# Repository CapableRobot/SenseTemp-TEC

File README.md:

# SenseTemp TEC

Designed by [Capable Robot Components](http://capablerobot.com).  
Follow us on [Twitter](http://twitter.com/capablerobot) for product announcements and updates.

---

**SenseTemp TEC is available for purchase at [CrowdSupply](https://www.crowdsupply.com/capable-robot-components/sensetemp) & [Mouser](https://www.mouser.com/ProductDetail/Crowd-Supply/cs-sensetemp-03?qs=sGAEpiMZZMsSgQ5oX0A7uhzs7btMGoRQYlEWJtksaKTgK6BSOcNH6Q%3D%3D).**  

## SenseTemp TEC Features 

## Specifications

## Feather Hosts

SenseTemp TEC is designed to mate with Adafruit Feather-compatible host modules, like:

* [Adafruit Feather M4 Express](https://www.adafruit.com/product/3857)
* [Adafruit Feather M0 Express](https://www.adafruit.com/product/3403)
* [Adafruit ESP32 Feather Host](https://www.adafruit.com/product/3405)

Note that the ES8266 Feather is **NOT** supported due to the limited IO on the ESP8266.  It does not have enough pins to support the four SPI devices of the SenseTemp.

## Software

## Hardware Revisions

* [CR2ERP](revisions/CR2ERP) : Released 2018-12-18.
	* Added high-side switch for fan control
	* Removed `!EN` pin as this product will not run off of battery power and there is no need to disable RTD converter chips.
	* Added 12v to 3v regulator (and disabled 5v to 3v regulator on host board).
	* Minor footprint changes.
	* Changed `PWM` pin for TEC control.
* [CRHVEF](revisions/CRHVEF) : Initial version released 2018-12-04.

## License Information

| **Type** | **License** |
| --- | --- |
| Hardware | Copyright Capable Robot Components 2018 <br><br>This documentation describes Open Hardware and is licensed under the [CERN OHL v1.2 or later](https://www.ohwr.org/licenses/cern-ohl/license_versions/v1.2). <br/><br/> You may redistribute and modify this documentation under the terms of the CERN OHL v.1.2.  This documentation is distributed WITHOUT ANY EXPRESS OR IMPLIED WARRANTY, INCLUDING OF MERCHANTABILITY, SATISFACTORY QUALITY AND FITNESS FOR A PARTICULAR PURPOSE. Please see the CERN OHL v.1.2 for applicable conditions |
| Software | [MIT License](tree/master/LICENSE.txt) |
| Documentation | [Creative Commons Attribution-ShareAlike](https://creativecommons.org/licenses/by-sa/4.0/) License |

More detailed information about the CERN License is available in the [license](license) folder and on the [CERN website](https://www.ohwr.org/projects/cernohl/wiki).

| **OSHW Certification** |

Coming Soon

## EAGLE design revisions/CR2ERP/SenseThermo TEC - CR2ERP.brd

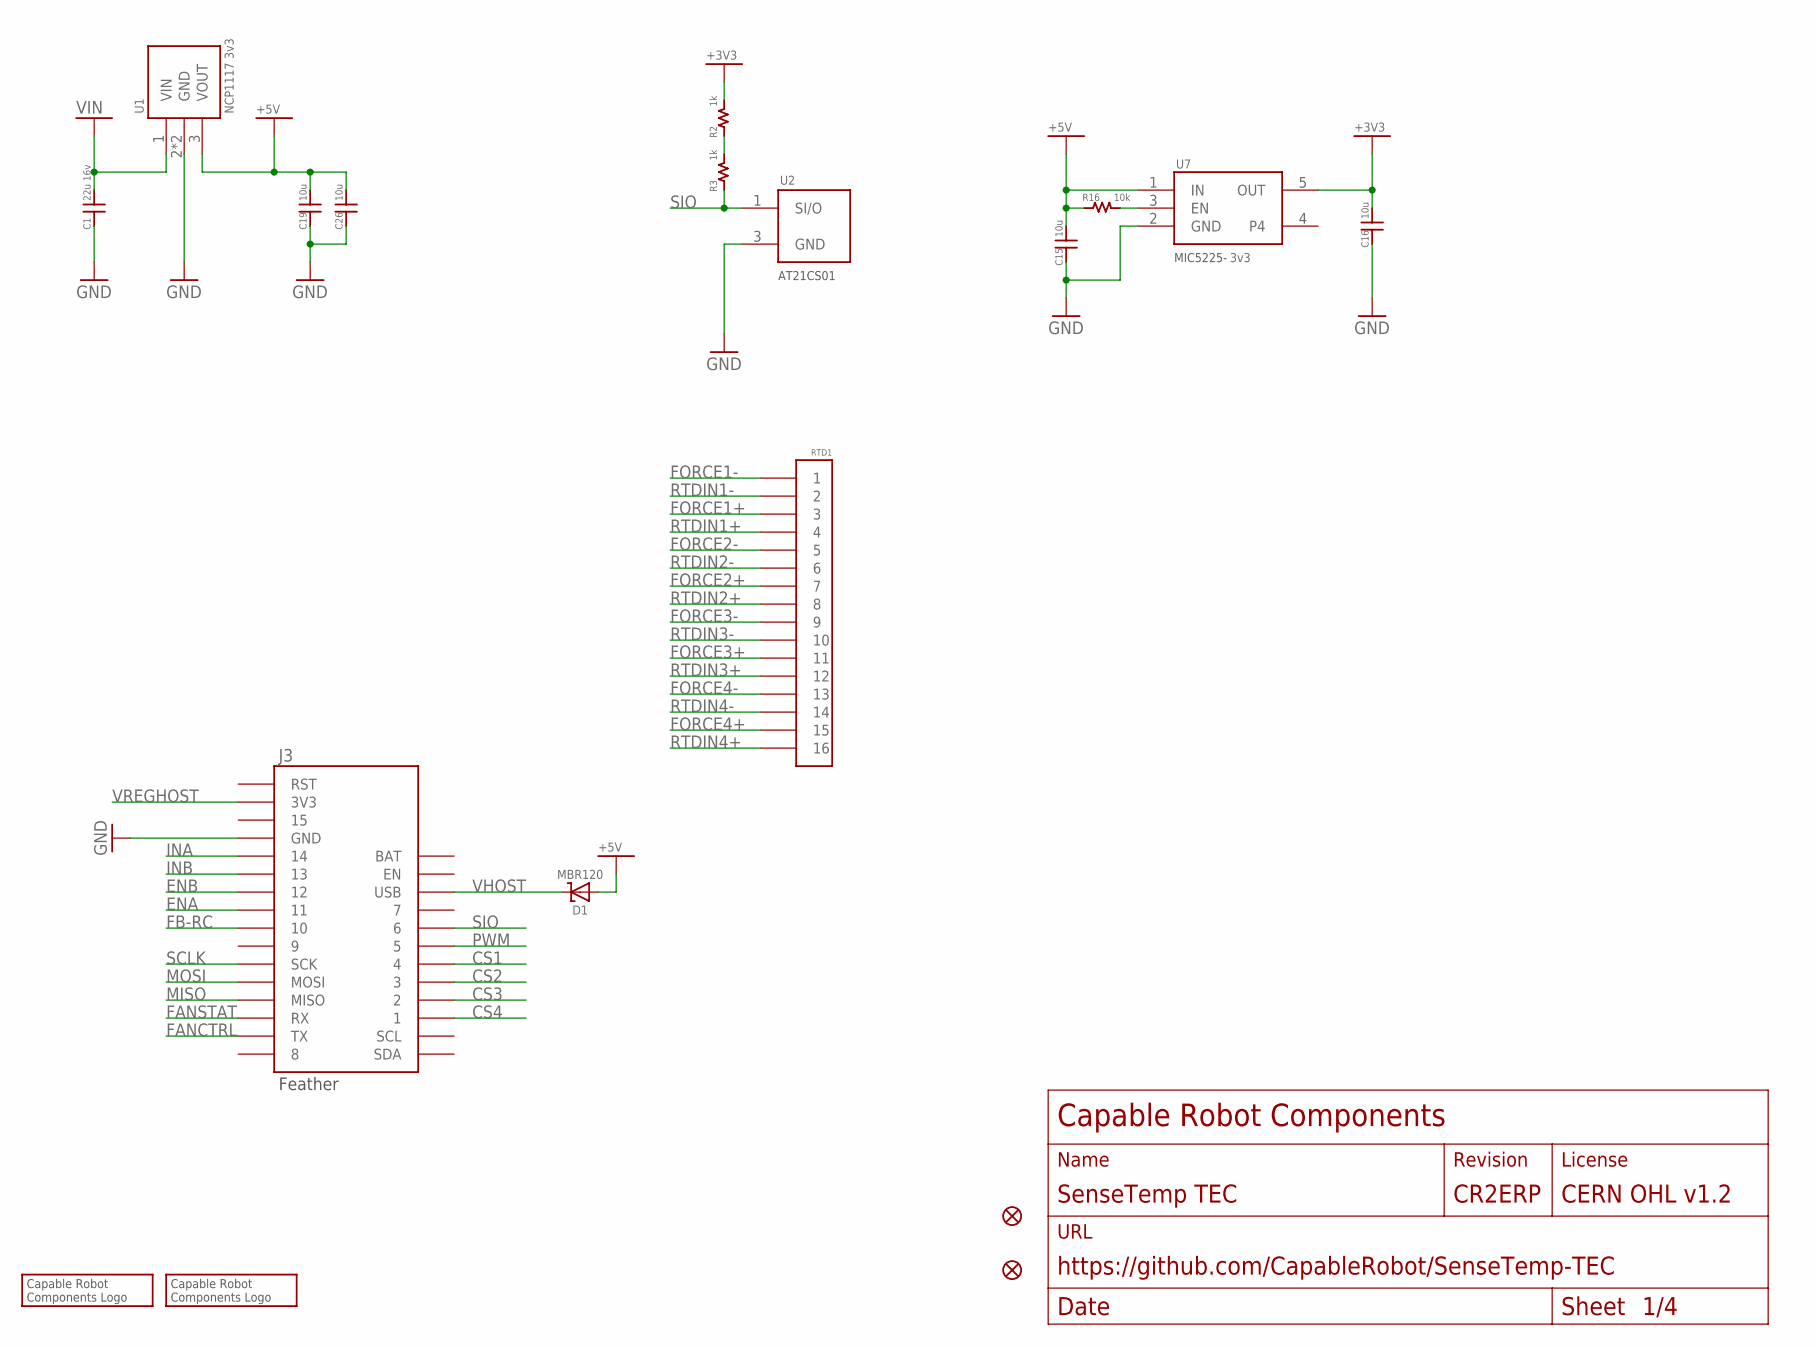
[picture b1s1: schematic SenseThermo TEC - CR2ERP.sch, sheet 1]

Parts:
C1: 22u 16v; 1206
C15, C16, C19, C26: 10u; 0805
D1: MBR120; SOD-123; MPN MBR120VLSFT3G
FID1, FID2: FIDUCIAL""; FIDUCIAL_1MM
J3: FEATHERPTH; FEATHER-PTH
LOGO1: CRC-LOGO7SILK; CRC-LOGO-7-SILK
LOGO2: CRC-LOGO5; CRC-LOGO-5
R2, R3: 1k; 0603
R16: 10k; 0603
RTD1: CONN-16ZT; CONN-2X8-050-SMT-ZT; MPN 3221-16-0300-00
U1: NCP1117 3v3; SOT230P700X180-4; MPN NCP1117ST50T3G
U2: AT21CS01; SOT23
U7: 3v3; SOT25

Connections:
+3V3: C16.P$2, R2.2, U7.5 (OUT); also elsewhere on the board
+5V: C15.P$2, C19.P$2, C26.P$2, D1.A, R16.1, U1.3 (VOUT), U7.1 (IN)
CS1: J3.4; also elsewhere on the board
CS2: J3.3; also elsewhere on the board
CS3: J3.2; also elsewhere on the board
CS4: J3.1; also elsewhere on the board
ENA: J3.11; also elsewhere on the board
ENB: J3.12; also elsewhere on the board
FANCTRL: J3.TX; also elsewhere on the board
FANSTAT: J3.RX; also elsewhere on the board
FB-RC: J3.10; also elsewhere on the board
FORCE1+: RTD1.3; also elsewhere on the board
FORCE1-: RTD1.1; also elsewhere on the board
FORCE2+: RTD1.7; also elsewhere on the board
FORCE2-: RTD1.5; also elsewhere on the board
FORCE3+: RTD1.11; also elsewhere on the board
FORCE3-: RTD1.9; also elsewhere on the board
FORCE4+: RTD1.15; also elsewhere on the board
FORCE4-: RTD1.13; also elsewhere on the board
GND: C1.P$1, C15.P$1, C16.P$1, C19.P$1, C26.P$1, J3.GND, U1.2 (GND), U1.4 (GND), U2.3 (GND), U7.2 (GND); also elsewhere on the board
INA: J3.14; also elsewhere on the board
INB: J3.13; also elsewhere on the board
MISO: J3.MISO; also elsewhere on the board
MOSI: J3.MOSI; also elsewhere on the board
unnamed: R2.1, R3.2
unnamed: R16.2, U7.3 (EN)
PWM: J3.5; also elsewhere on the board
RTDIN1+: RTD1.4; also elsewhere on the board
RTDIN1-: RTD1.2; also elsewhere on the board
RTDIN2+: RTD1.8; also elsewhere on the board
RTDIN2-: RTD1.6; also elsewhere on the board
RTDIN3+: RTD1.12; also elsewhere on the board
RTDIN3-: RTD1.10; also elsewhere on the board
RTDIN4+: RTD1.16; also elsewhere on the board
RTDIN4-: RTD1.14; also elsewhere on the board
SCLK: J3.SCK; also elsewhere on the board
SIO: J3.6, R3.1, U2.1 (SI/O)
VHOST: D1.C, J3.USB
VIN: C1.P$2, U1.1 (VIN); also elsewhere on the board
VREGHOST: J3.3V3; also elsewhere on the board

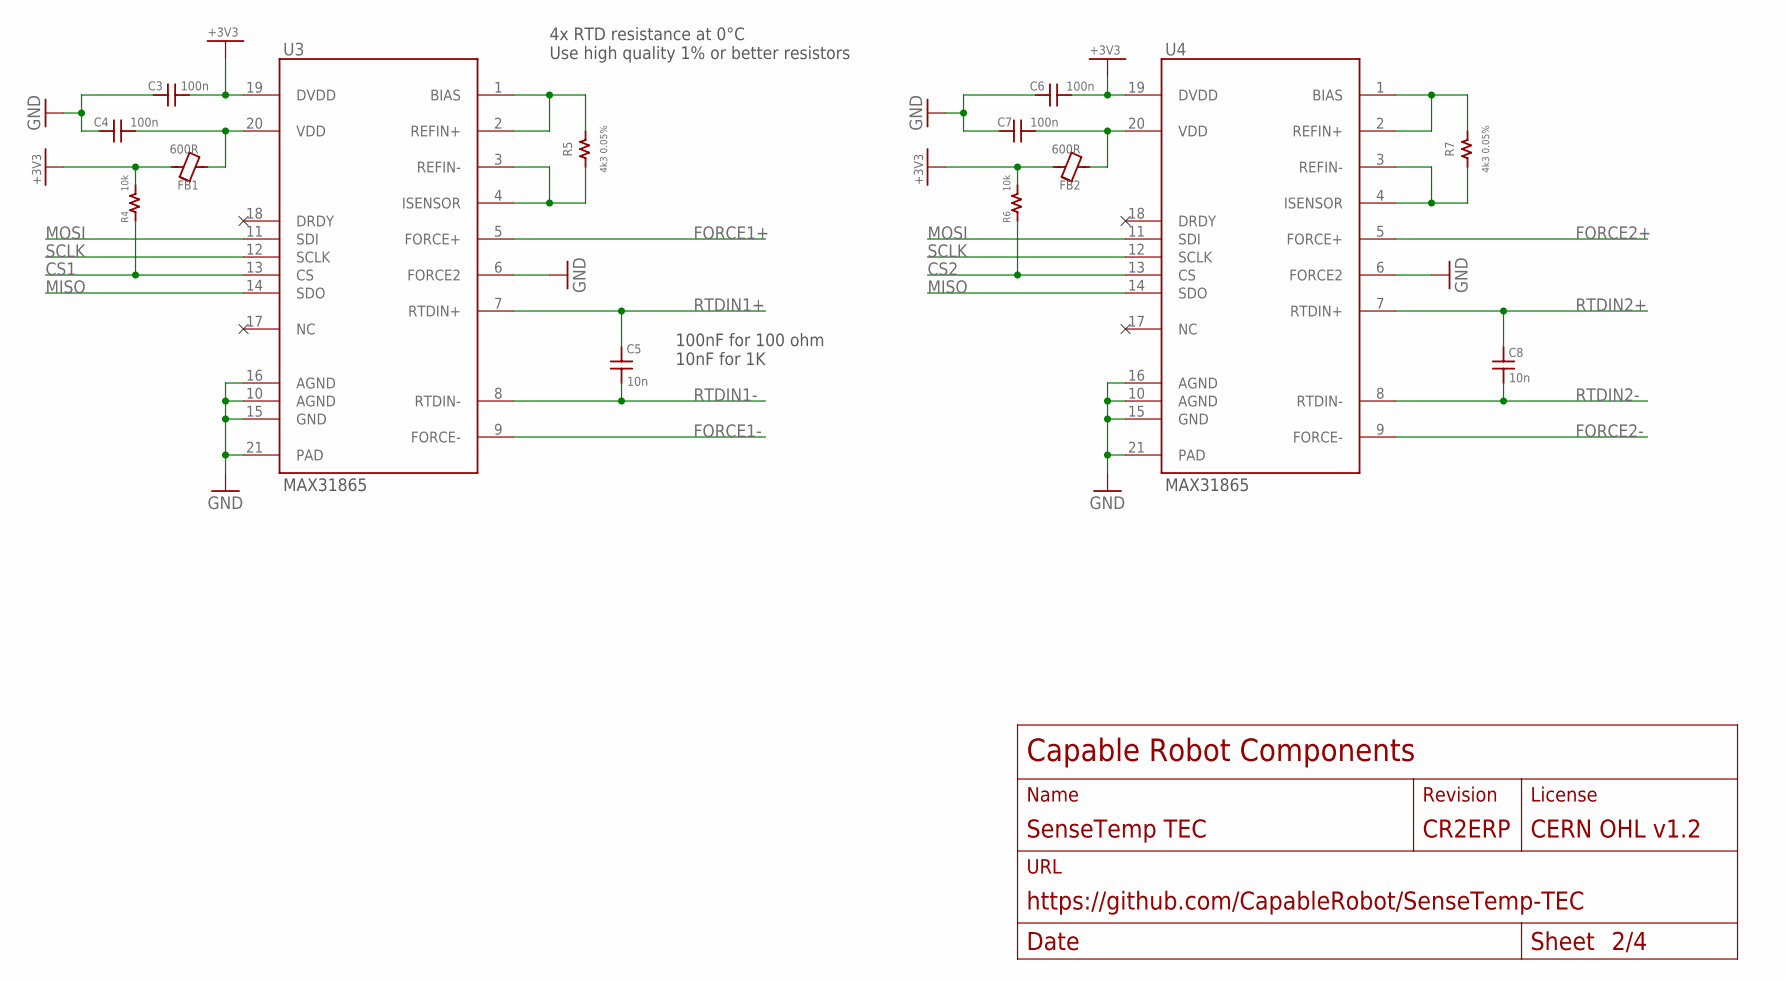
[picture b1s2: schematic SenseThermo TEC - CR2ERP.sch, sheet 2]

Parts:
C3, C4, C6, C7: 100n; 0603
C5, C8: 10n; 0603
FB1, FB2: 600R; 0603
R4, R6: 10k; 0603
R5, R7: 4k3 0.05%; 0603
U3, U4: MAX31865; QFN65P500X500X100-21T325

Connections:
+3V3: C3.1, C6.1, FB1.2, FB2.2, R4.2, R6.2, U3.19 (DVDD), U4.19 (DVDD); also elsewhere on the board
CS1: R4.1, U3.13 (CS); also elsewhere on the board
CS2: R6.1, U4.13 (CS); also elsewhere on the board
FORCE1+: U3.5 (FORCE+); also elsewhere on the board
FORCE1-: U3.9 (FORCE-); also elsewhere on the board
FORCE2+: U4.5 (FORCE+); also elsewhere on the board
FORCE2-: U4.9 (FORCE-); also elsewhere on the board
GND: C3.2, C4.2, C6.2, C7.2, U3.6 (FORCE2), U3.10 (AGND), U3.15 (GND), U3.16 (AGND), U3.21 (PAD), U4.6 (FORCE2), U4.10 (AGND), U4.15 (GND), U4.16 (AGND), U4.21 (PAD); also elsewhere on the board
MISO: U3.14 (SDO), U4.14 (SDO); also elsewhere on the board
MOSI: U3.11 (SDI), U4.11 (SDI); also elsewhere on the board
unnamed: R5.2, U3.1 (BIAS), U3.2 (REFIN+)
unnamed: R5.1, U3.3 (REFIN-), U3.4 (ISENSOR)
unnamed: C4.1, FB1.1, U3.20 (VDD)
unnamed: R7.2, U4.1 (BIAS), U4.2 (REFIN+)
unnamed: R7.1, U4.3 (REFIN-), U4.4 (ISENSOR)
unnamed: C7.1, FB2.1, U4.20 (VDD)
RTDIN1+: C5.1, U3.7 (RTDIN+); also elsewhere on the board
RTDIN1-: C5.2, U3.8 (RTDIN-); also elsewhere on the board
RTDIN2+: C8.1, U4.7 (RTDIN+); also elsewhere on the board
RTDIN2-: C8.2, U4.8 (RTDIN-); also elsewhere on the board
SCLK: U3.12 (SCLK), U4.12 (SCLK); also elsewhere on the board

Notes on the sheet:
4x RTD resistance at 0°C Use high quality 1% or better resistors
100nF for 100 ohm 10nF for 1K

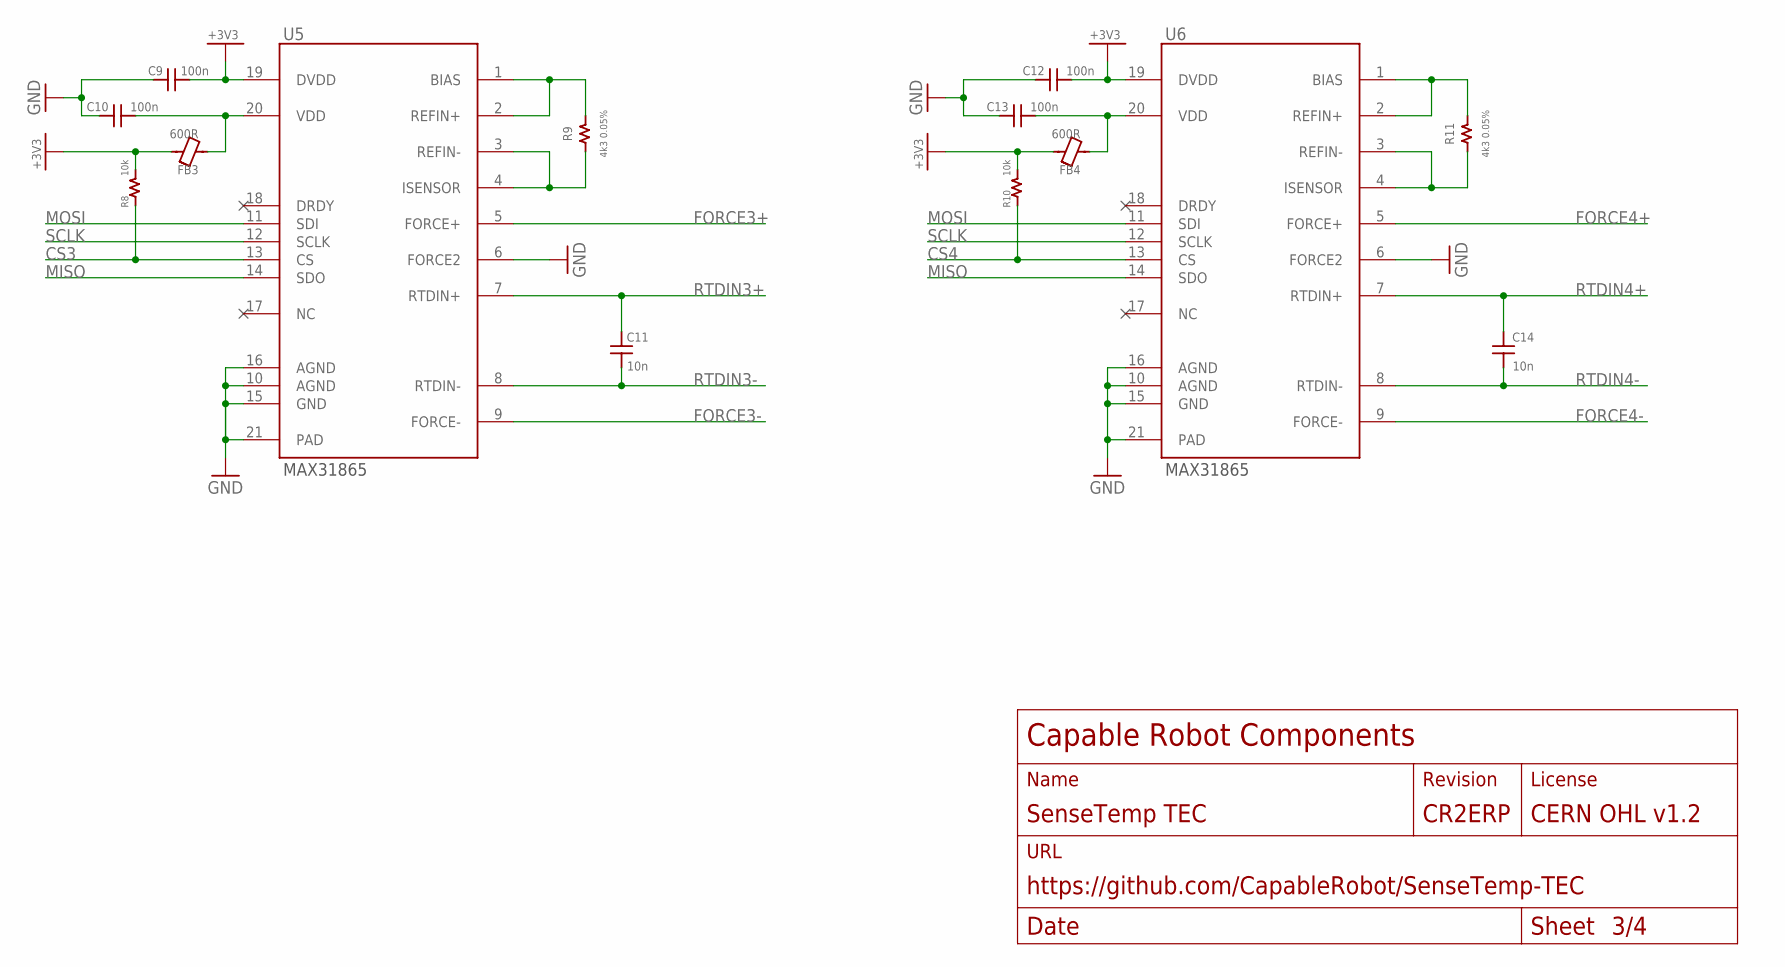
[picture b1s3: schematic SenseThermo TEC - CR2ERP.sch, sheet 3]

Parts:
C9, C10, C12, C13: 100n; 0603
C11, C14: 10n; 0603
FB3, FB4: 600R; 0603
R8, R10: 10k; 0603
R9, R11: 4k3 0.05%; 0603
U5, U6: MAX31865; QFN65P500X500X100-21T325

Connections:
+3V3: C9.1, C12.1, FB3.2, FB4.2, R8.2, R10.2, U5.19 (DVDD), U6.19 (DVDD); also elsewhere on the board
CS3: R8.1, U5.13 (CS); also elsewhere on the board
CS4: R10.1, U6.13 (CS); also elsewhere on the board
FORCE3+: U5.5 (FORCE+); also elsewhere on the board
FORCE3-: U5.9 (FORCE-); also elsewhere on the board
FORCE4+: U6.5 (FORCE+); also elsewhere on the board
FORCE4-: U6.9 (FORCE-); also elsewhere on the board
GND: C9.2, C10.2, C12.2, C13.2, U5.6 (FORCE2), U5.10 (AGND), U5.15 (GND), U5.16 (AGND), U5.21 (PAD), U6.6 (FORCE2), U6.10 (AGND), U6.15 (GND), U6.16 (AGND), U6.21 (PAD); also elsewhere on the board
MISO: U5.14 (SDO), U6.14 (SDO); also elsewhere on the board
MOSI: U5.11 (SDI), U6.11 (SDI); also elsewhere on the board
unnamed: R9.2, U5.1 (BIAS), U5.2 (REFIN+)
unnamed: R9.1, U5.3 (REFIN-), U5.4 (ISENSOR)
unnamed: C10.1, FB3.1, U5.20 (VDD)
unnamed: R11.2, U6.1 (BIAS), U6.2 (REFIN+)
unnamed: R11.1, U6.3 (REFIN-), U6.4 (ISENSOR)
unnamed: C13.1, FB4.1, U6.20 (VDD)
RTDIN3+: C11.1, U5.7 (RTDIN+); also elsewhere on the board
RTDIN3-: C11.2, U5.8 (RTDIN-); also elsewhere on the board
RTDIN4+: C14.1, U6.7 (RTDIN+); also elsewhere on the board
RTDIN4-: C14.2, U6.8 (RTDIN-); also elsewhere on the board
SCLK: U5.12 (SCLK), U6.12 (SCLK); also elsewhere on the board

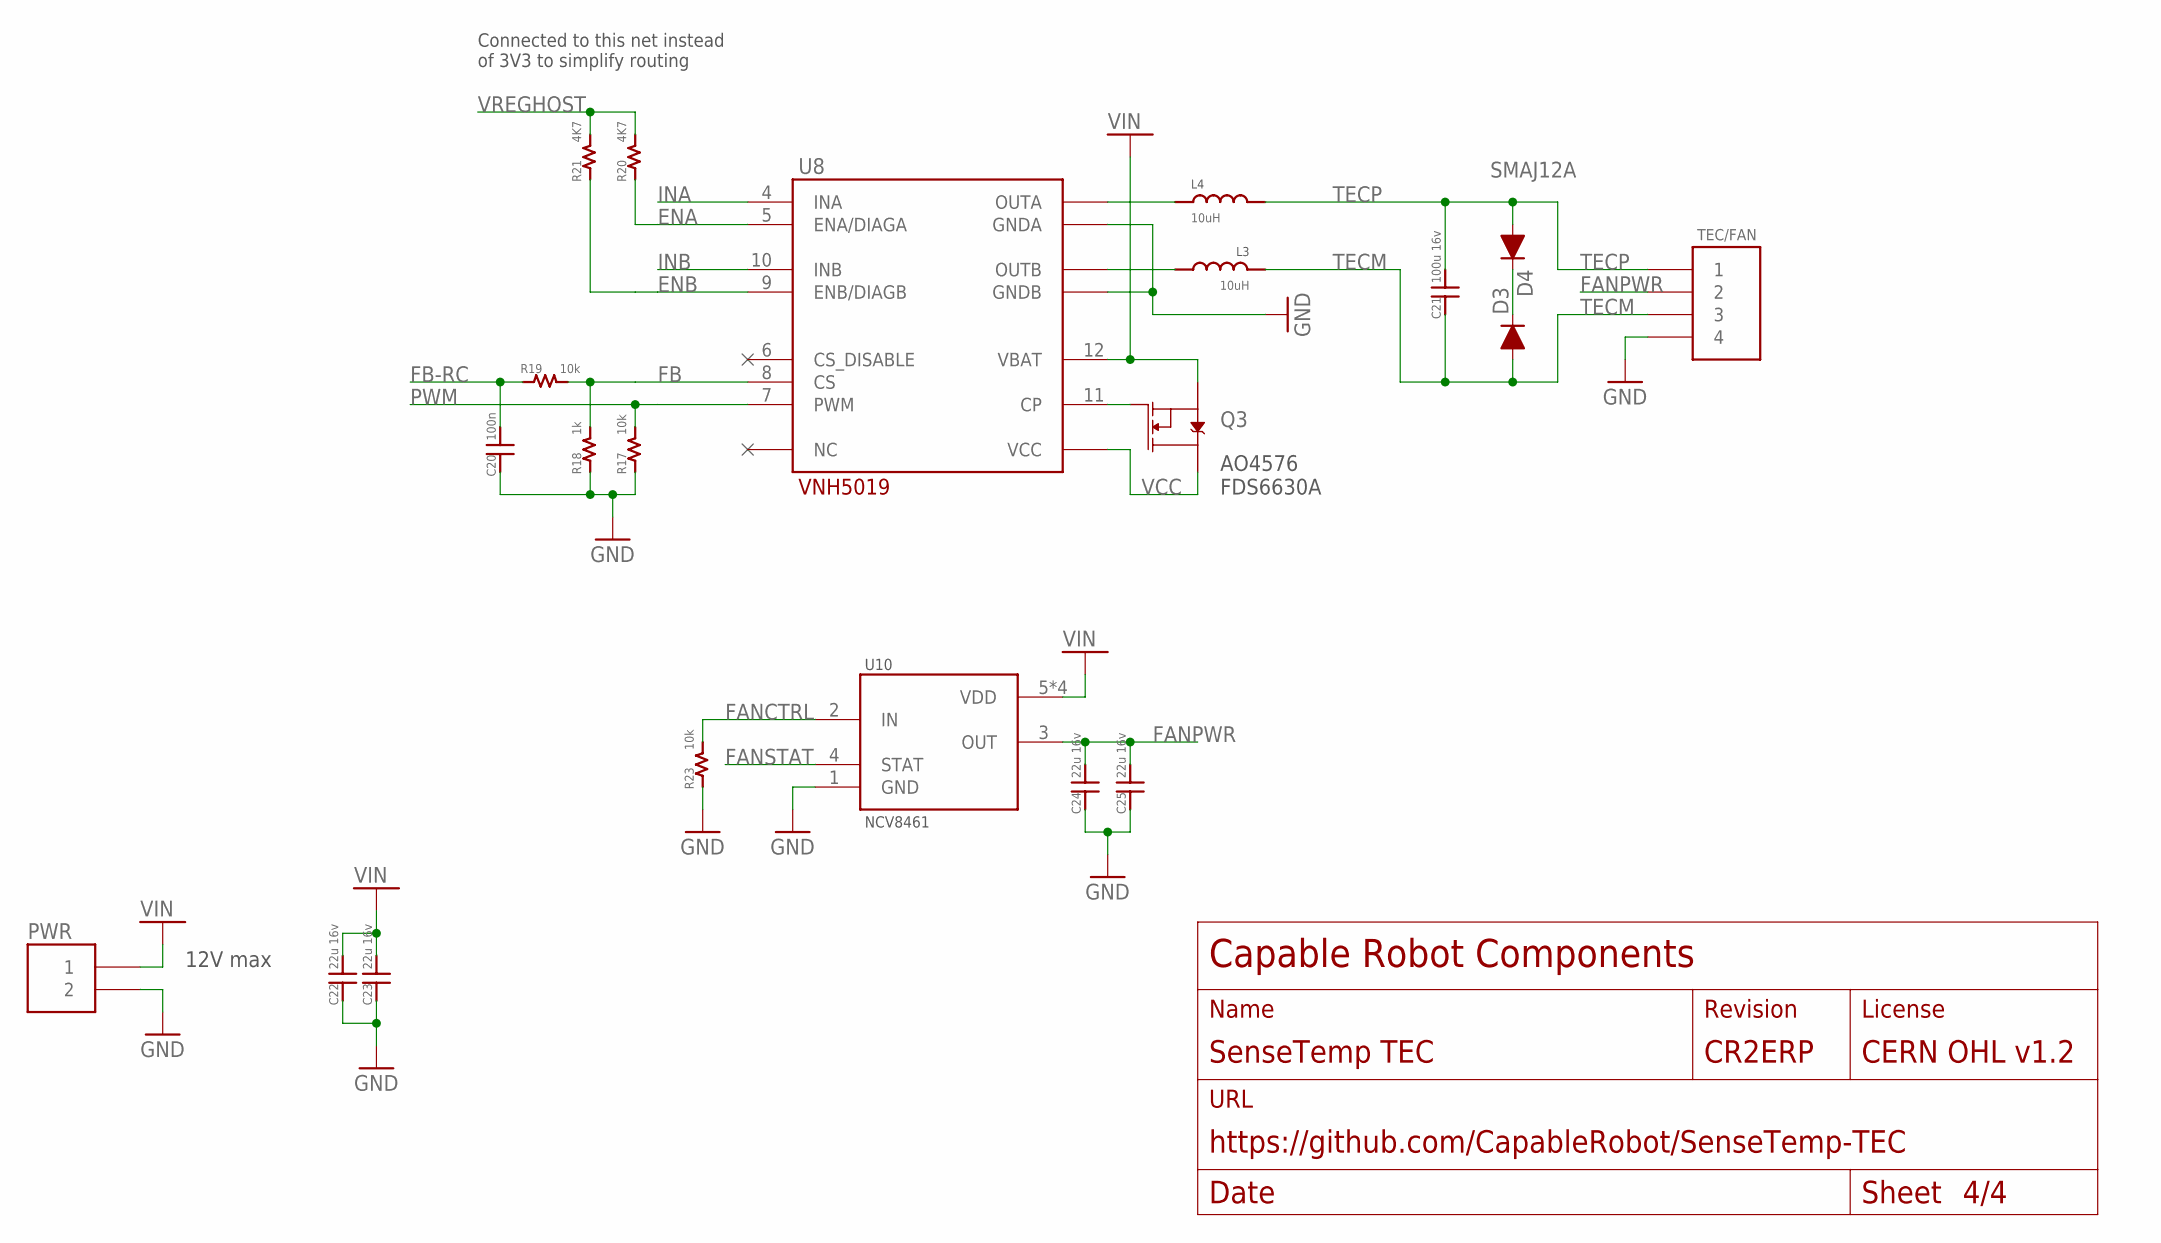
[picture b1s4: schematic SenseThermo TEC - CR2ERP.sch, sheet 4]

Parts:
C20: 100n; 0603
C21: 100u 16v; 2220
C22, C23, C24, C25: 22u 16v; 1206
D3, D4: SMAJ12A; DO214AA; MPN SMAJ12A-13-F
L3, L4: 10uH; IND-HCF1007
PWR: CONN-2-MFJR-RA; CONN-MFJR-RA-2X1
Q3: 6.5A/30V/38mΩ; SOIC127P600X175-8; MPN FDS6630A
R17, R19, R23: 10k; 0603
R18: 1k; 0603
R20, R21: 4K7; 0603
TEC/FAN: CONN-4-MFJR-RA; CONN-MFJR-RA-2X2
U8: VNH5019; SOP100P1900X235-30-EP
U10: NCV8461; SOIC127P600X175-8; MPN NCV8461DR2G

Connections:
CP1: Q3.4 (G), U8.11 (CP)
ENA: R20.1, U8.5 (ENA/DIAGA); also elsewhere on the board
ENB: R21.1, U8.9 (ENB/DIAGB); also elsewhere on the board
FANCTRL: R23.2, U10.2 (IN); also elsewhere on the board
FANPWR: C24.P$2, C25.P$2, TEC/FAN.2, U10.3 (OUT)
FANSTAT: U10.4 (STAT); also elsewhere on the board
FB: R18.2, R19.2, U8.8 (CS)
FB-RC: C20.2, R19.1; also elsewhere on the board
GND: C20.1, C22.P$1, C23.P$1, C24.P$1, C25.P$1, PWR.2, R17.1, R18.1, R23.1, TEC/FAN.4, U8.18 (GNDB), U8.19 (GNDB), U8.20 (GNDB), U8.26 (GNDA), U8.27 (GNDA), U8.28 (GNDA), U10.1 (GND); also elsewhere on the board
INA: U8.4 (INA); also elsewhere on the board
INB: U8.10 (INB); also elsewhere on the board
OUTA1: L4.1, U8.1 (OUTA), U8.25 (OUTA), U8.30 (OUTA), U8.OUTA
OUTB1: L3.2, U8.15 (OUTB), U8.16 (OUTB), U8.21 (OUTB), U8.OUTB
PWM: R17.2, U8.7 (PWM); also elsewhere on the board
SNUB1: D3.C, D4.C
TECM: C21.1, D3.A, L3.1, TEC/FAN.3
TECP: C21.2, D4.A, L4.2, TEC/FAN.1
VCC: Q3.5 (D), Q3.6 (D), Q3.7 (D), Q3.8 (D), U8.3 (VCC), U8.13 (VCC), U8.23 (VCC), U8.VCC
VIN: C22.P$2, C23.P$2, PWR.1, Q3.1 (S), Q3.2 (S), Q3.3 (S), U8.12 (VBAT), U10.5 (VDD), U10.6 (VDD), U10.7 (VDD), U10.8 (VDD); also elsewhere on the board
VREGHOST: R20.2, R21.2; also elsewhere on the board

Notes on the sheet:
12V max
AO4576 FDS6630A
Connected to this net instead of 3V3 to simplify routing

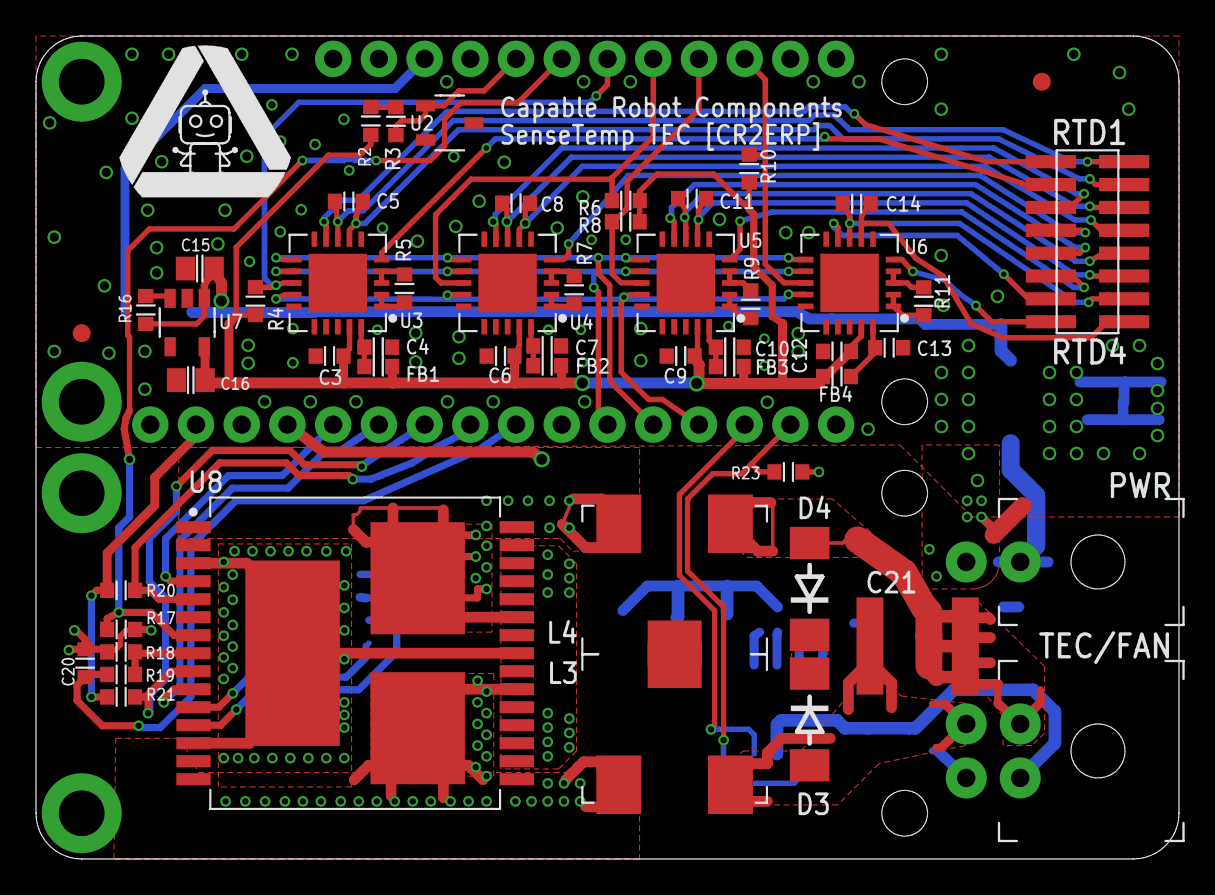
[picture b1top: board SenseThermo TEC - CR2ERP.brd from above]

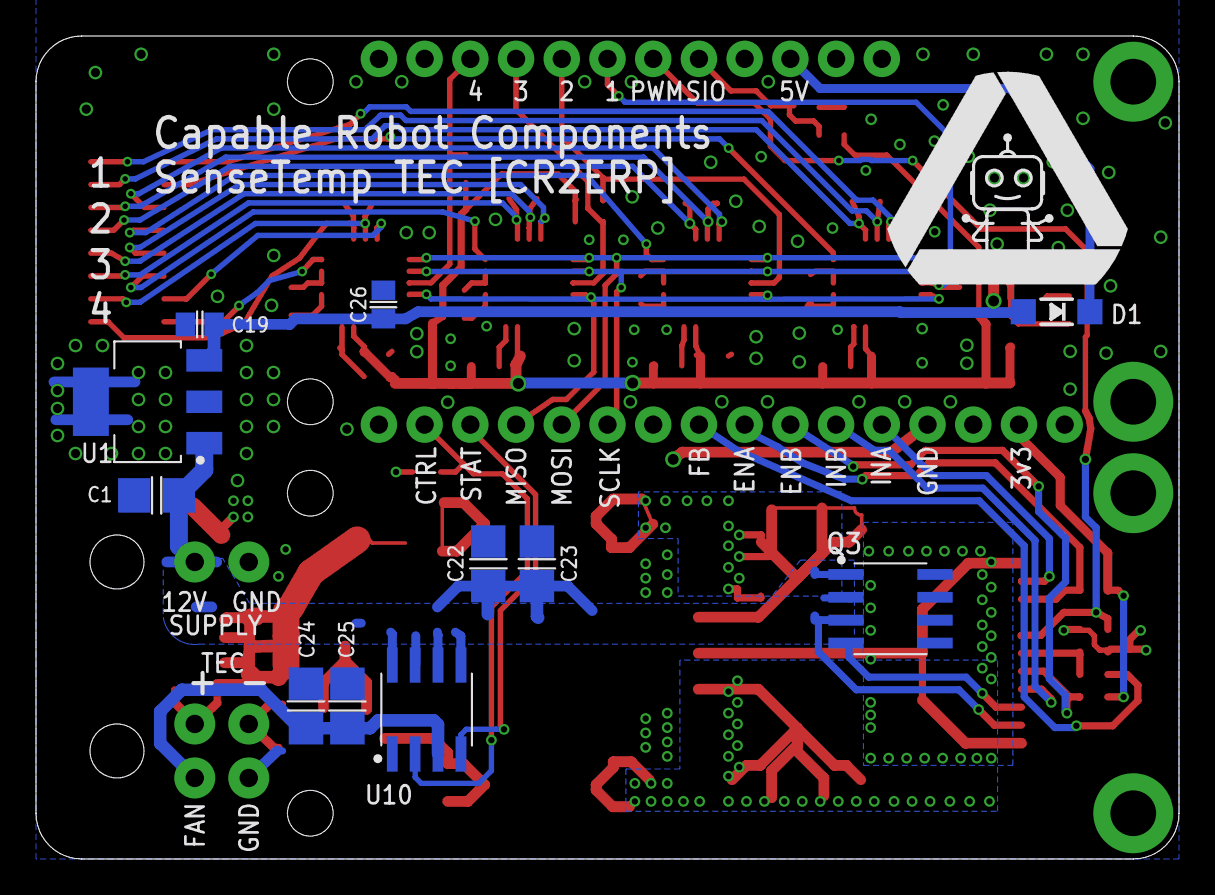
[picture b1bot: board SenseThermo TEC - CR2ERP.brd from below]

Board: 2 copper layers, 63.5 x 45.7 mm, 67 parts (12 on the bottom side), 61 nets.

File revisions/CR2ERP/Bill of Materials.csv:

Name,Mpn,Count,Device,Value,Package,Mfg,Cost,Description
"C1,C22,C23,C24,C25",CL31X226KOHN3NE,5,CAP-1206,22u 16v,1206,Samsung,0.9049,""
"C15,C16,C19,C26",CL21A106KPFNNNE,4,CAP-0805,10u,0805,Samsung,0.19060000000000002,""
C21,CKG57NX7S1C107M500JH,1,CAP-2220,100u 16v,2220,TDK,3.2068,""
"C3,C4,C6,C7,C9,C10,C12,C13,C20",MF-CAP-0603-0.1uF,9,CAP-0603,100n,0603,Generic,,""
"C5,C8,C11,C14",MF-CAP-0603-0.01uF,4,CAP-0603,10n,0603,Generic,,""
D1,MBR120VLSFT3G,1,DIODE-SCHOTTKY-SOD-123,MBR120,SOD-123,ON Semiconductor,0.16,""
"D3,D4",SMAJ12A-13-F,2,DIODE-DO214AA,SMAJ12A,DO214AA,Diodes Inc.,0.236,""
"FB1,FB2,FB3,FB4",BK1608HW601-T,4,FER-0603,600R,0603,Taiyo Yuden,0.11350000000000002,""
"L3,L4",HCF1007-100-R,2,IND-HCF1007,10uH,IND-HCF1007,Eaton,4.3222,""
PWR,43045-0200,1,CONN-2-MFJR-RA,,CONN-MFJR-RA-2X1,Molex,0.7328,""
Q3,FDS6630A,1,MOSFET-NCH-SOIC8,6.5A/30V/38mΩ,SOIC127P600X175-8,ON Semiconductor,0.316,""
"R2,R3,R18",MF-RES-0603-1K,3,RES-0603,1k,0603,Generic,,""
"R20,R21",MF-RES-0603-4.7K,2,RES-0603,4K7,0603,Generic,,""
"R4,R6,R8,R10,R16,R17,R19,R23",MF-RES-0603-10K,8,RES-0603,10k,0603,Generic,,""
"R5,R7,R9,R11",ERA3ARW432V,4,RES-0603,4k3 0.05%,0603,Panasonic,1.7916,""
RTD1,3221-16-0300-00,1,CONN-16-ZT,,CONN-2X8-050-SMT-ZT,CNC Tech,0.946,""
TEC/FAN,43045-0400,1,CONN-4-MFJR-RA,,CONN-MFJR-RA-2X2,Molex,1.1052,""
U1,NCP1117ST50T3G,1,VREG-LDO,NCP1117 3v3,SOT230P700X180-4,ON Semiconductor,0.238,""
U10,NCV8461DR2G,1,NCV8461,,SOIC127P600X175-8,ON Semiconductor,0.753,""
U2,AT21CS01-STUM10-T,1,AT21CS01,,SOT23,Microchip,0.1836,""
"U3,U4,U5,U6",MAX31865ATP+,4,MAX31865,,QFN65P500X500X100-21T325,Maxim Integrated,12.336,""
U7,AP2112K-3.3TRG1,1,MIC5225,3v3,SOT25,Diodes Inc.,0.15,""
U8,VNH5019ATR-E,1,VNH5019,,SOP100P1900X235-30-EP,STMicroelectronics,5.75,""

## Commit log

2018-12-18 Rename license file
2018-12-18 Adding CRHVEF prototype version.
2018-12-19 Initial commit of CR2ERP version. Fixed footprint of MAX31865 RTD ICs
2018-12-19 Remove 5v to 3v regulator (will be replaced by 12v to 3v regulator. Change TEC PWM pin.
2018-12-19 Added 12v to 5v regulator and 5v to 3v regulators. Changed RTD passives to 0603
2018-12-19 Added high side switch for fan. Silkscreen changes.
2018-12-19 Adding top and bottom renders
2018-12-19 Adding CERN OHL license folder
2018-12-19 Add ignore file
2018-12-19 Move R8 away from U5
2019-08-13 Update to released version of CR2ERP
2019-08-13 Added CircuitPython VNH5019 library and example usage code
2019-10-25 Remove extraneous files

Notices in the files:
revisions/CR2ERP/SenseThermo TEC - CR2ERP.sch:
LICENSE: CERN OHL v1.2
parts and their libraries:
microbuilder: This work is placed in the public domain, and may be freely used for commercial and non-commercial work with the following conditions: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
